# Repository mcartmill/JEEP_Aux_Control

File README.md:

# JEEP_Aux_Control
Control for aux accessories like additional lighting using a touchscreen control.

Goal

I am creating an open source solution to controlling additional electronic components such as lights.  

Conditions:
1.    Must be stand alone, not connecting to existing systems of the Jeep.
2.    Easy to customize
3.    Low Cost
4.    All documents available for anyone to use (code, PCB files, GRB files)
5.    Allow others to add to the documentation for functionality and defects

____________________________________________________________________________________
MCU Code

Code uses Ardiuno code for ease of use.
Jeep_AUX_Control.ino.ino

____________________________________________________________________________________
Touchscreen Code

Since using Nextion screen, UI code uses Nextion Editor Software - Free and easy to use.

____________________________________________________________________________________

Power Circuit code

Code for power circuit using ATTiny85 - attiny85powerlogicv0.1.ino

Power Circuit Theory of Operations

12V constant and 12V switched (identified as ignition in this document) comes into the circuit.  These are regulated down to 5V constant, 5V ignition, and 5V Ignition w/Delay off.

ATTiny85 is used to control 5V Ignition w/Delay by monitoring 5V Ignition into digital pin 0.  When digital pin 0 goes low, the chip sees this as ignition is off and then runs a delay and then sets digital pin 1 to low, which is the output that controls a transistor as a switch for the 5V Ignition w/Delay.

ATTiny85 Pinout
Pin4 = GND
Pin5= Digital Pin 0 = Input from 5V ignition
Pin6= Digital Pin 1 = Output to control transistor for delayed 5V ignition
Pin8= VCC (5V Constant)

Theory of Operations for ATTiny85 Code

Digital Pin0 = input
Digital Pin1 = output = init high

While pin0 is low then pin1==LOW

____________________________________________________________________________________
PCB

PCB files made in Eagle CAD.  Include ready to print files for https://jlcpcb.com/

Power Circuit PCB - power reg 5v_2019-04-10.zip

Control PCB JEEP_Aux_Control_PCB.brd and JEEP_Aux_Control_PCB.sch
JEEP_Aux_Control_PCB_2020-09-06.zip is the complete cam output to send to PCB house for production

____________________________________________________________________________________
BOM

BOM along with sources for parts
 
Control Board BOM
https://www.mouser.com/ProjectManager/ProjectDetail.aspx?AccessID=32fda13301

Power Board BOM
https://www.mouser.com/ProjectManager/ProjectDetail.aspx?AccessID=7aa37e28ff
 
Touchscreen
https://www.amazon.com/Nextion-NX4024T032-Display-Arduino-Raspberry/dp/B07QYRB38T/ref=sr_1_5?dchild=1&keywords=nextion+display&qid=1599437750&sr=8-5
 
Relays
https://www.amazon.com/ONLINE-LED-STORE-Pack-Interlocking/dp/B01KVZ2MU4/ref=sr_1_8?crid=1BJ267T4AIGVN&dchild=1&keywords=bosch+relay+12v&qid=1599437842&sprefix=bosch+relay%2Caps%2C187&sr=8-8

____________________________________________________________________________________
3D models

____________________________________________________________________________________
Github file location:

https://github.com/mcartmill/JEEP_Aux_Control

____________________________________________________________________________________
Youtube videos

https://youtu.be/mUTJI6I0mCo

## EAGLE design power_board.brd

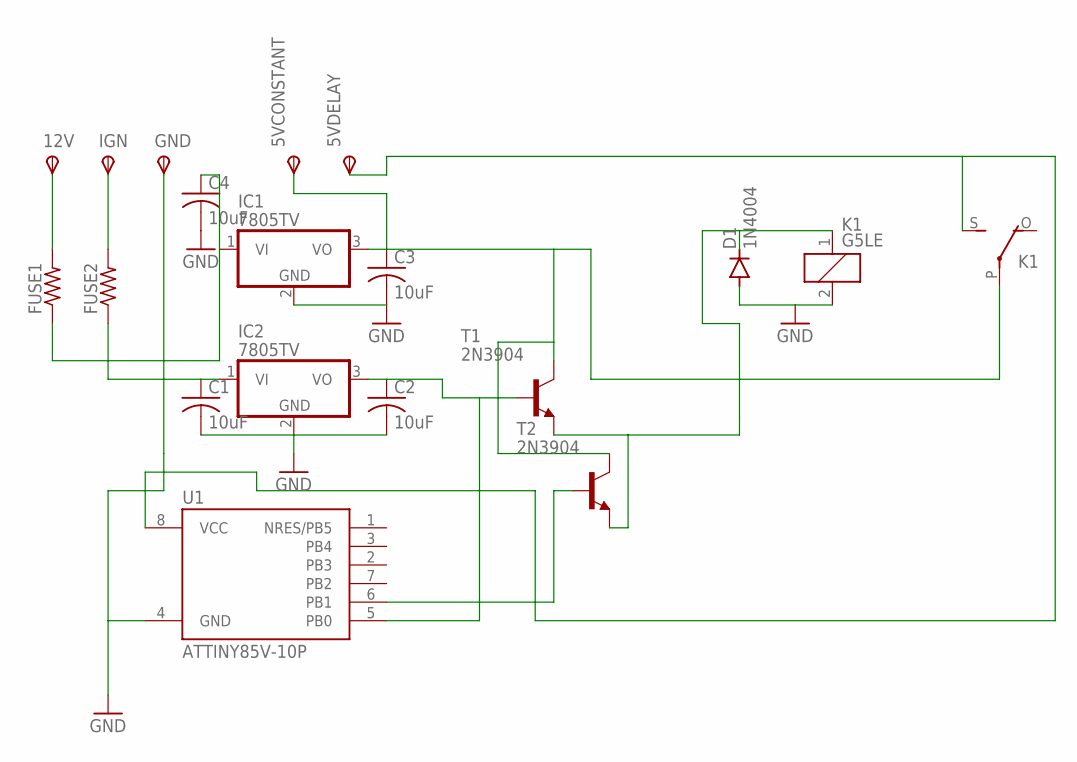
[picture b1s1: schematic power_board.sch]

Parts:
5VCONSTANT, 5VDELAY, 12V: TPSPAD1-13Y; P1-13Y
C1, C2, C3, C4: 10uF; C0603
D1: 1N4004; DO41-10
FUSE1, FUSE2: R-US_R0805; R0805
GND: TPSPAD1-13Y; P1-13Y
IC1, IC2: 7805TV; TO220V
IGN: TPSPAD1-13Y; P1-13Y
K1: G5LE
T1, T2: 2N3904; TO92
U1: ATTINY85V-10P; PDIP08_300MIL

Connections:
GND: C1.2, C2.2, C3.2, C4.2, D1.A, GND.TP, IC1.2 (GND), IC2.2 (GND), K1.2, U1.4 (GND)
unnamed: 12V.TP, FUSE1.2
unnamed: FUSE2.2, IGN.TP
unnamed: C1.1, FUSE2.1, IC2.1 (VI)
unnamed: C4.1, FUSE1.1, IC1.1 (VI)
unnamed: C2.1, IC2.3 (VO), T1.2 (B), U1.5 (PB0)
unnamed: 5VCONSTANT.TP, C3.1, IC1.3 (VO), K1.P, T1.1 (C), T2.1 (C)
unnamed: D1.C, K1.1, T1.3 (E), T2.3 (E)
unnamed: 5VDELAY.TP, K1.S, U1.8 (VCC)
unnamed: T2.2 (B), U1.6 (PB1)

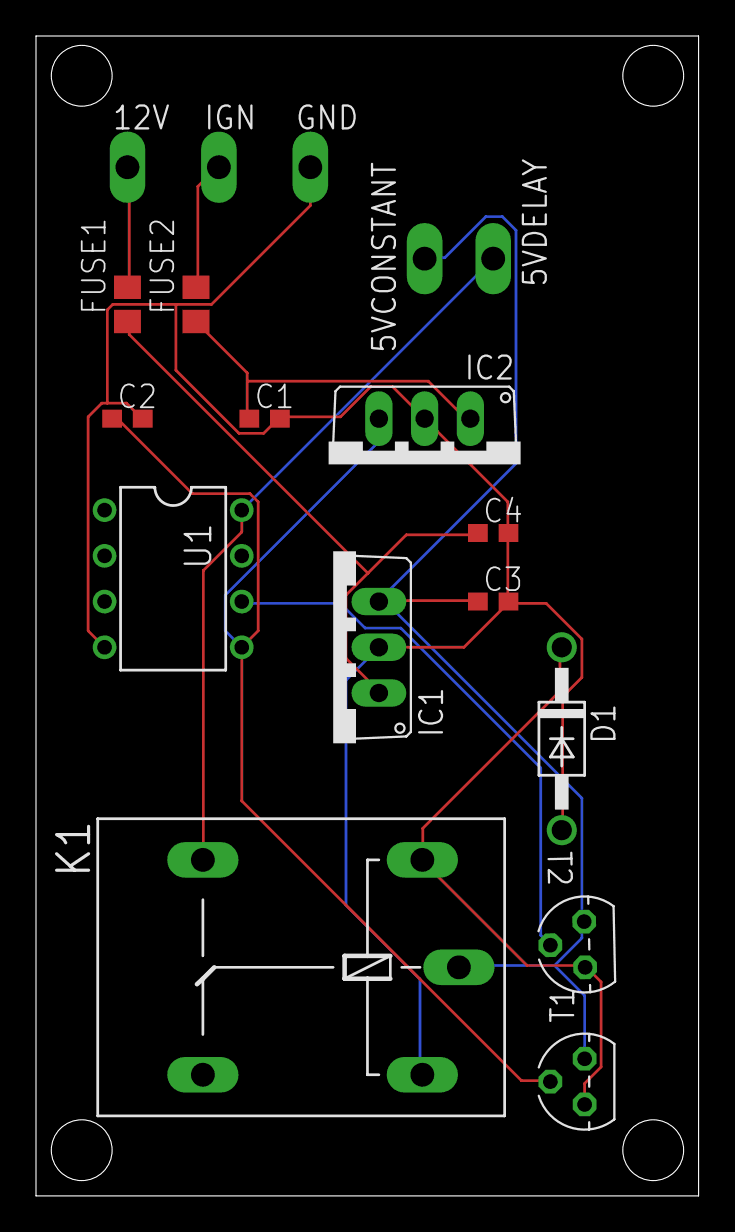
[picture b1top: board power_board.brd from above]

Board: 2 copper layers, 36.8 x 64.4 mm, 18 parts (0 on the bottom side), 10 nets.

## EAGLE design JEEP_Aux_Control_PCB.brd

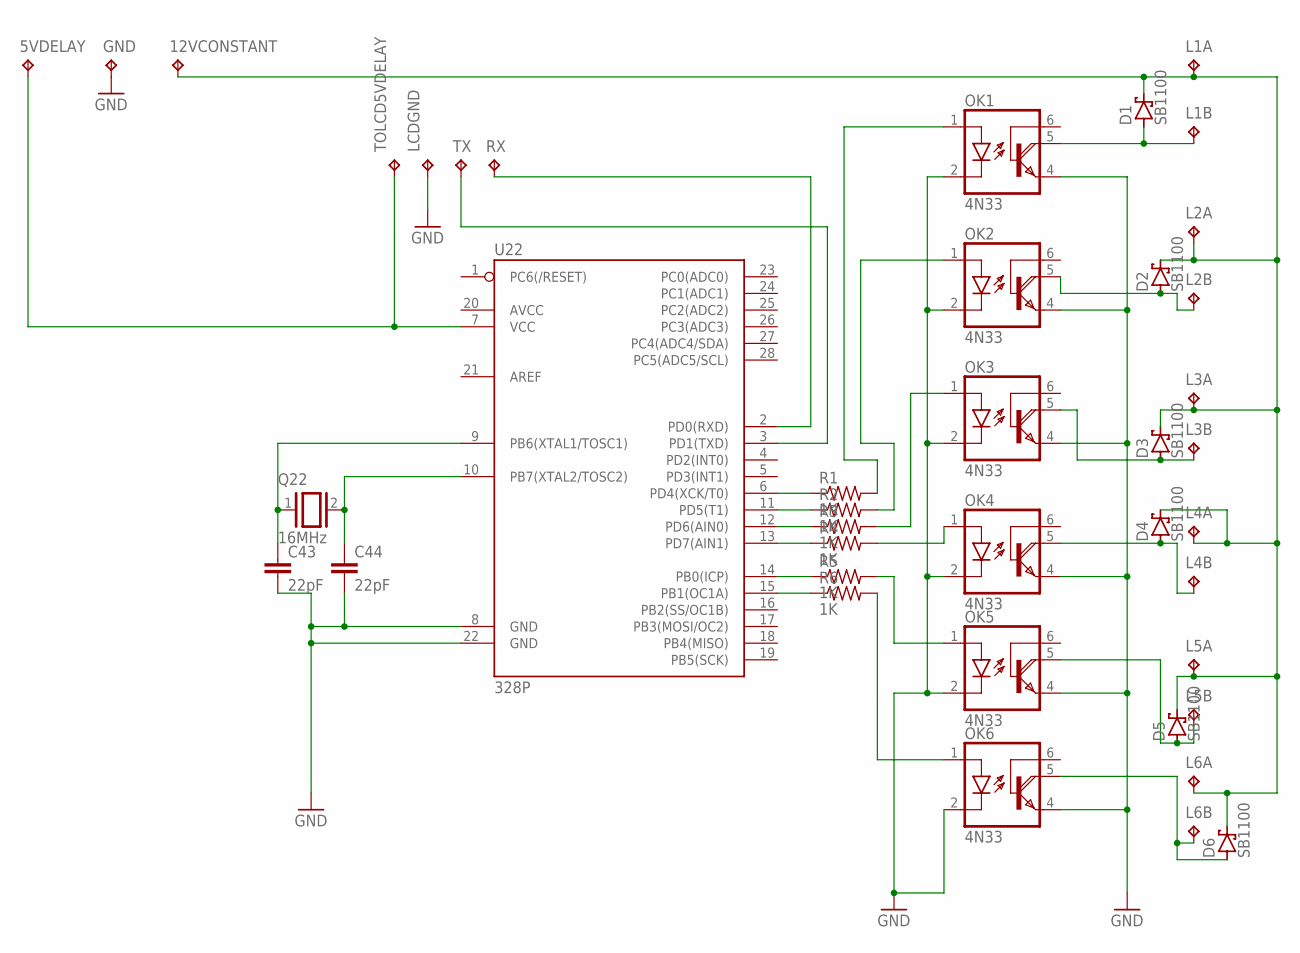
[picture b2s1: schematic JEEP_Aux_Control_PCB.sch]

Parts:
5VDELAY, 12VCONSTANT: TPPAD1-13Y; P1-13Y
C43, C44: 22pF; CAP-PTH-2.54
D1, D2, D3, D4, D5, D6: SB1100; CB417-15
GND: TPPAD1-13Y; P1-13Y
L1A, L1B, L2A, L2B, L3A, L3B, L4A, L4B, L5A, L5B, L6A, L6B: TPPAD1-13Y; P1-13Y
LCDGND: TPPAD1-13Y; P1-13Y
OK1, OK2, OK3, OK4, OK5, OK6: 4N33; DIL06
Q22: 16MHz; Q
R1, R2, R3, R4, R5, R6: 1K; R0603
RX: TPPAD1-13Y; P1-13Y
TOLCD5VDELAY: TPPAD1-13Y; P1-13Y
TX: TPPAD1-13Y; P1-13Y
U22: 328P; DIP28

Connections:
GND: C43.2, C44.2, GND.TP, LCDGND.TP, OK1.2 (C), OK1.4 (E), OK2.2 (C), OK2.4 (E), OK3.2 (C), OK3.4 (E), OK4.2 (C), OK4.4 (E), OK5.2 (C), OK5.4 (E), OK6.2 (C), OK6.4 (E), U22.8 (GND), U22.22 (GND)
unnamed: R1.1, U22.6 (PD4(XCK/T0))
unnamed: R2.1, U22.11 (PD5(T1))
unnamed: R3.1, U22.12 (PD6(AIN0))
unnamed: R4.1, U22.13 (PD7(AIN1))
unnamed: R5.1, U22.14 (PB0(ICP))
unnamed: R6.1, U22.15 (PB1(OC1A))
unnamed: OK1.1 (A), R1.2
unnamed: OK2.1 (A), R2.2
unnamed: OK3.1 (A), R3.2
unnamed: OK4.1 (A), R4.2
unnamed: OK5.1 (A), R5.2
unnamed: OK6.1 (A), R6.2
unnamed: D1.A, L1B.TP, OK1.5 (COL)
unnamed: D2.A, L2B.TP, OK2.5 (COL)
unnamed: D3.A, L3B.TP, OK3.5 (COL)
unnamed: D4.A, L4B.TP, OK4.5 (COL)
unnamed: D5.A, L5B.TP, OK5.5 (COL)
unnamed: D6.A, L6B.TP, OK6.5 (COL)
unnamed: TX.TP, U22.3 (PD1(TXD))
unnamed: 5VDELAY.TP, TOLCD5VDELAY.TP, U22.7 (VCC)
unnamed: RX.TP, U22.2 (PD0(RXD))
unnamed: 12VCONSTANT.TP, D1.C, D2.C, D3.C, D4.C, D5.C, D6.C, L1A.TP, L2A.TP, L3A.TP, L4A.TP, L5A.TP, L6A.TP
unnamed: C43.1, Q22.1, U22.9 (PB6(XTAL1/TOSC1))
unnamed: C44.1, Q22.2, U22.10 (PB7(XTAL2/TOSC2))

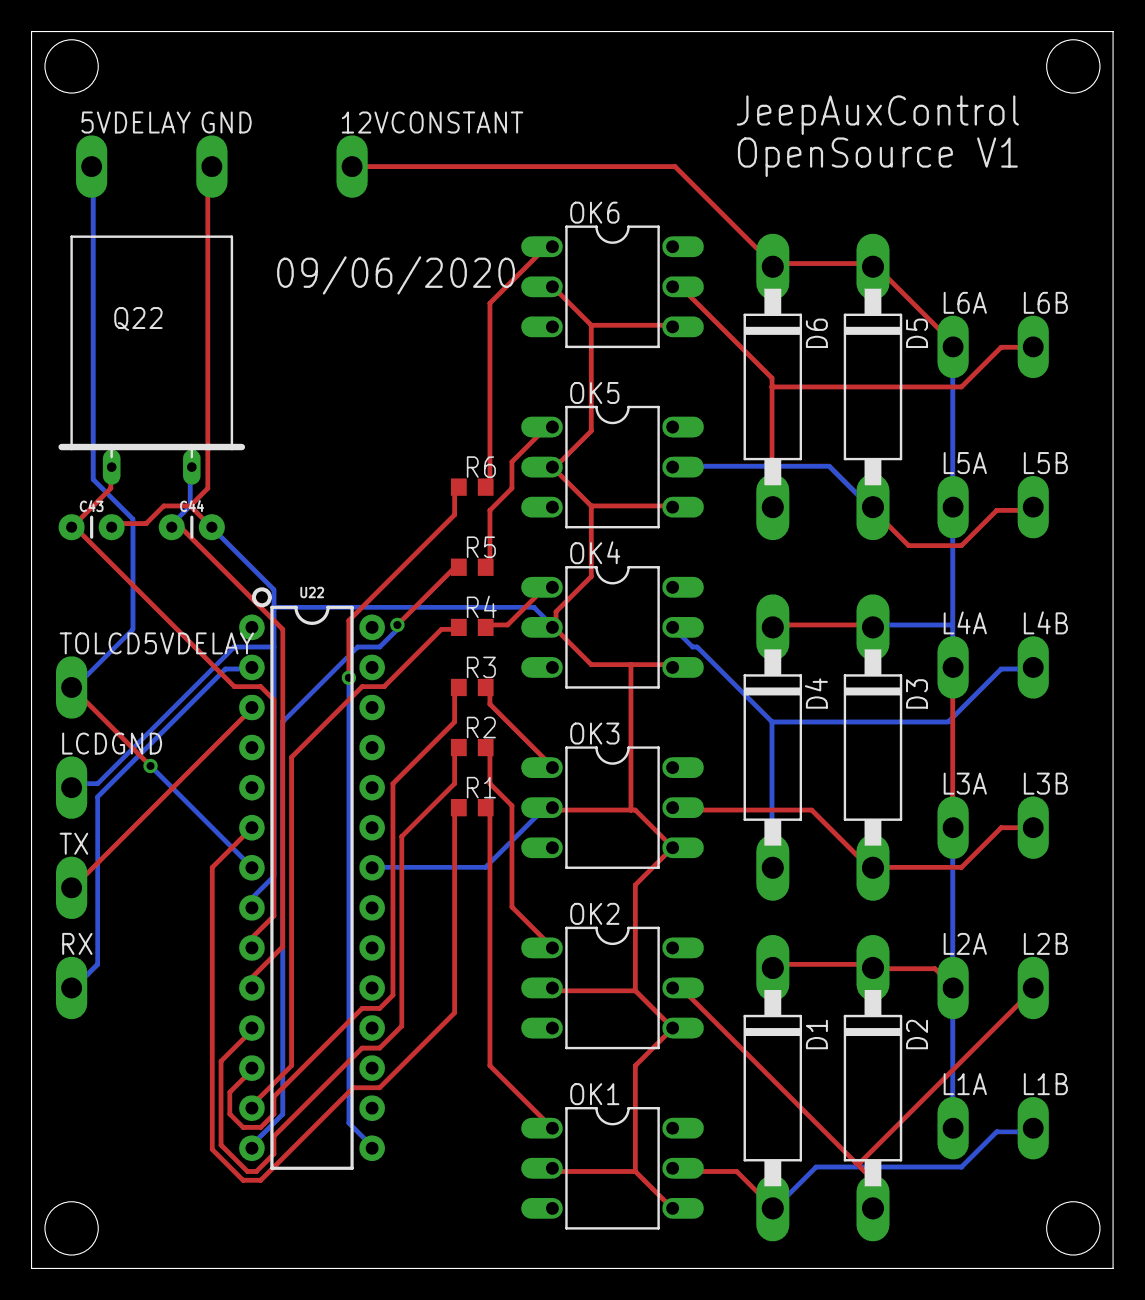
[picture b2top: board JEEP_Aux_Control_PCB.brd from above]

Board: 2 copper layers, 68.6 x 78.4 mm, 41 parts (0 on the bottom side), 25 nets.

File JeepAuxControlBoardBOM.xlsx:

JEEP AUX CONTROL
Mouser # | Mfr. # | Manufacturer | Customer # | Description | RoHS | Lifecycle | Order Qty. | Price (USD) | Ext.: (USD)
512-SB1100 | SB1100 | ON Semiconductor |  | Schottky Diodes & Rectifiers Schottky Diode | RoHS Compliant |  | 6.0 | $0.36 | $2.16
559-FOXSD160-20-LF | FOXSDLF/160-20 | Fox |  | Crystals 16MHz 20pF | RoHS Compliant |  | 1.0 | $0.27 | $0.27
581-06035A220J | 06035A220JAT2A | AVX |  | Multilayer Ceramic Capacitors MLCC - SMD/SMT 50V 22pF C0G 0603 5% | RoHS Compliant |  | 2.0 | $0.10 | $0.20
556-ATMEGA328P-PU | ATMEGA328P-PU | Microchip |  | 8-bit Microcontrollers - MCU 32KB In-system Flash 20MHz 1.8V-5.5V | RoHS Compliant |  | 1.0 | $2.08 | $2.08
571-1-2199298-9 | 1-2199298-9 | TE Connectivity |  | IC & Component Sockets 28P DIP SKT 300 CL LADDER | RoHS Compliant |  | 1.0 | $0.46 | $0.46
594-MCT0603PD1001DP5 | MCT0603PD1001DP500 | Vishay |  | Thin Film Resistors - SMD .250W 1Kohms .5% 0603 25ppm Hi Power | RoHS Compliant By Exemption |  | 6.0 | $0.57 | $3.42
78-4N32 | 4N32 | Vishay |  | Transistor Output Optocouplers Photodarlington Out | RoHS Compliant |  | 6.0 | $0.65 | $3.90

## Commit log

2020-08-30 update of readme
    Update of readme - start of thorough details for users/editors
2020-08-30 Initial upload of grb files for Power PCB
2020-08-30 Power Cirucuit Code
    Code for ATTiny85 in power circuit
2020-08-30 Update README.md
    Added Power circuit PCB files and Power Circuit ATTiny85 code
2020-08-30 Initial Control PCB Design
2020-08-30 updated to distinguish control PCB files
2020-08-31 updated with new youtube video link
2020-08-31 ATMEL MCU code - initial
2020-08-31 added MCU code for control on ATMEL 328
2020-09-06 control schematic update
2020-09-06 Cleanup of schematic
2020-09-06 PCB update for v1
    v1 Control PCB - submitted to PCB house
2020-09-07 update of BOM
2020-09-07 Updated BOM info
2020-09-07 Updated JeepControl PCB CAM info
2020-09-07 update of powerboard docs
2020-09-07 PowerBoard PCB
2020-09-09 power board update

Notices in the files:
parts and their libraries:
SparkFun-Capacitors: Licensing: Creative Commons ShareAlike 4.0 International - https://creativecommons.org/licenses/by-sa/4.0
